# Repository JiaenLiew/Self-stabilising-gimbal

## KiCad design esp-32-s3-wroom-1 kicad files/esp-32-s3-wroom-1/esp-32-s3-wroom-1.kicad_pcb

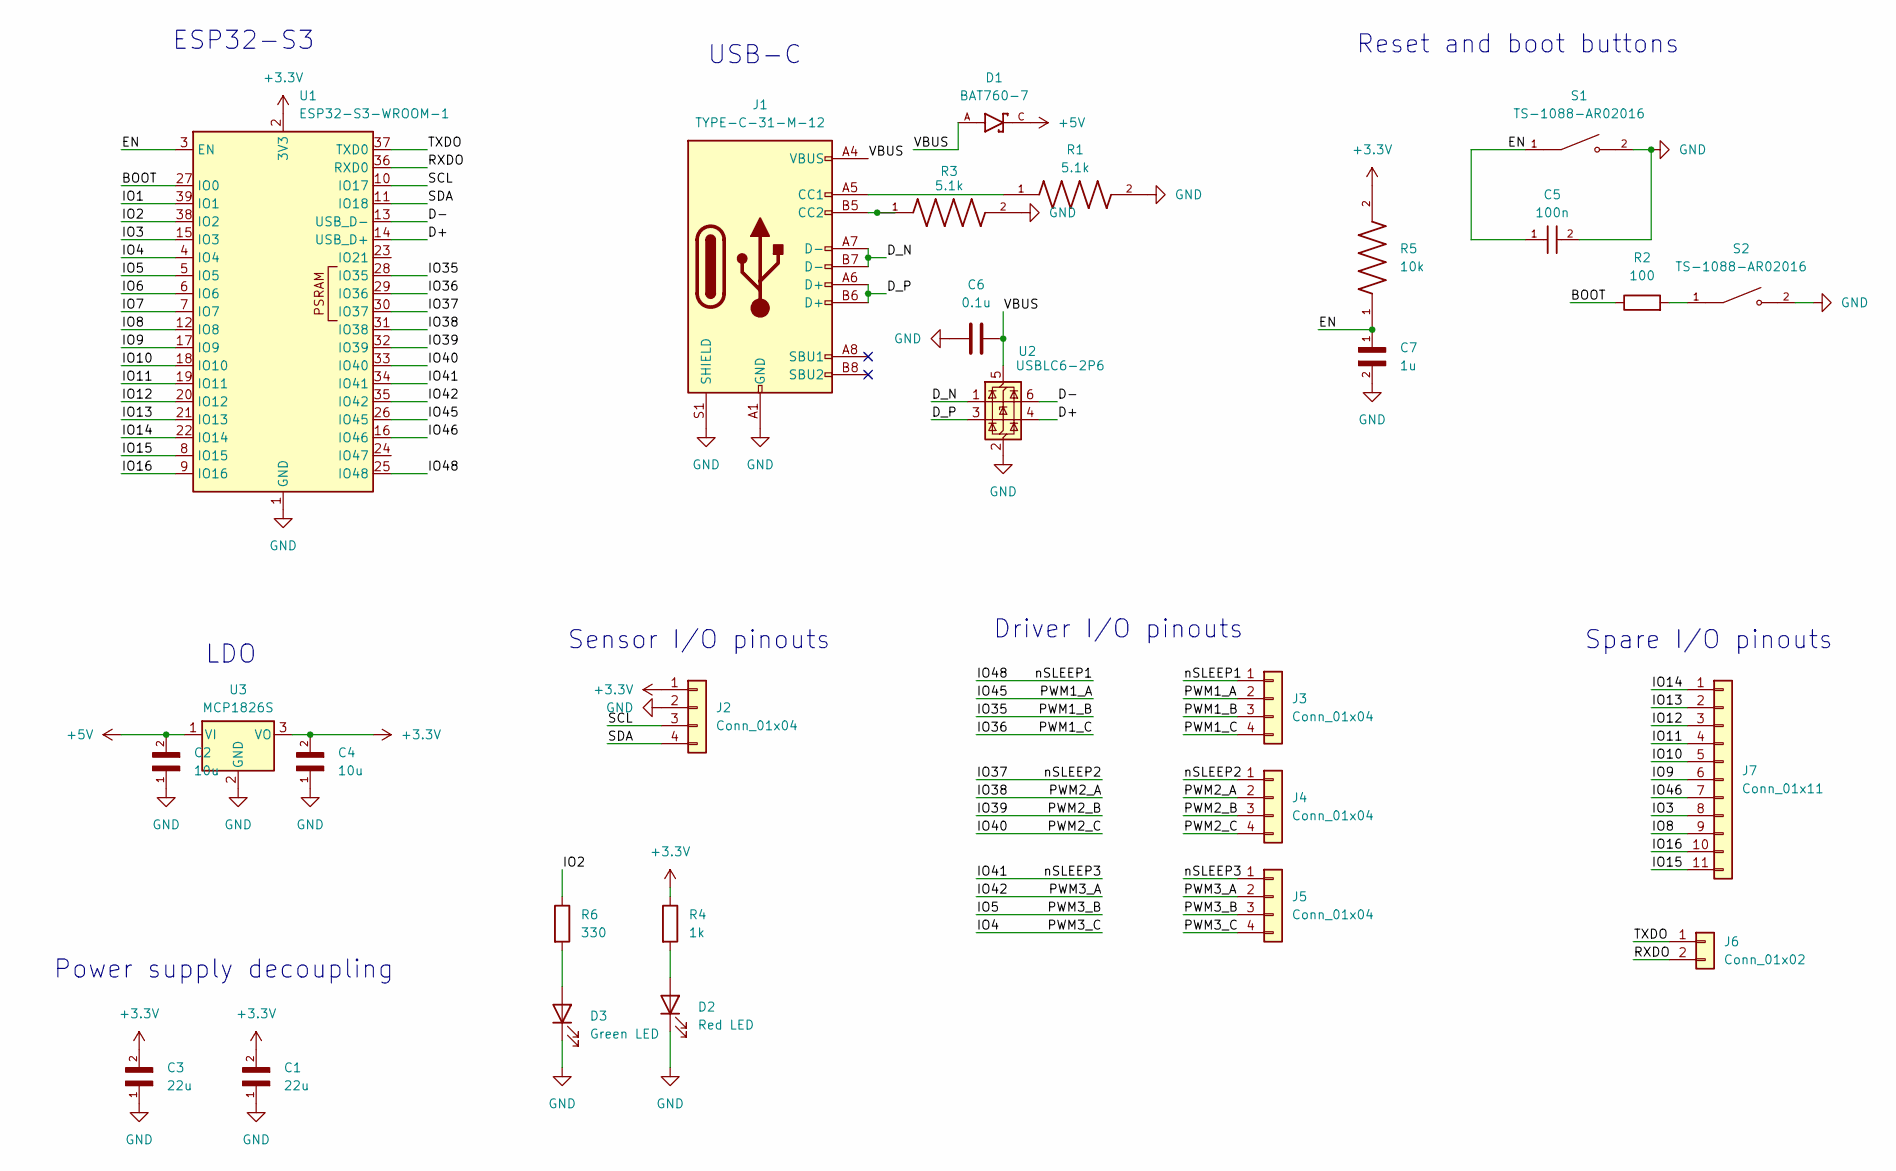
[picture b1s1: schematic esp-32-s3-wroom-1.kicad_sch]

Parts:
C1, C3: 22u; C_0805_2012Metric_Pad1.18x1.45mm_HandSolder
C2, C4: 10u; C_0805_2012Metric_Pad1.18x1.45mm_HandSolder
C5: 100n; C_0805_2012Metric_Pad1.18x1.45mm_HandSolder; DigiKey_Part_Number 732-7478-2-ND
C6: 0.1u; C_0805_2012Metric_Pad1.18x1.45mm_HandSolder
C7: 1u; C_0805_2012Metric_Pad1.18x1.45mm_HandSolder; DigiKey_Part_Number 490-5810-2-ND
D1: BAT760-7; SOD2513X120N; PARTREV 9-2
D2: Red LED; LED_0805_2012Metric_Pad1.15x1.40mm_HandSolder
D3: Green LED; LED_0805_2012Metric_Pad1.15x1.40mm_HandSolder
J1: TYPE-C-31-M-12; USB_C_Receptacle_HRO_TYPE-C-31-M-12
J2, J3, J4, J5: Conn_01x04; PinHeader_1x04_P2.54mm_Vertical
J6: Conn_01x02; PinHeader_1x02_P2.54mm_Vertical
J7: Conn_01x11; PinHeader_1x11_P2.54mm_Vertical
R1: 5.1k; R_0805_2012Metric_Pad1.20x1.40mm_HandSolder; PARTREV 3/1/2020; DigiKey_Part_Number P5.1KBRTR-ND
R2: 100; R_0805_2012Metric_Pad1.20x1.40mm_HandSolder
R3: 5.1k; C_0805_2012Metric_Pad1.18x1.45mm_HandSolder; PARTREV 3/1/2020; DigiKey_Part_Number P5.1KBRTR-ND
R4: 1k; R_0805_2012Metric_Pad1.20x1.40mm_HandSolder
R5: 10k; R_0805_2012Metric_Pad1.20x1.40mm_HandSolder; Voltage_Rating 50 V; Tolerance 5%; DigiKey_Part_Number A106045TR-ND
R6: 330; R_0805_2012Metric_Pad1.20x1.40mm_HandSolder
S1, S2: TS-1088-AR02016; SW_TS-1088-AR02016; PARTREV N/A
U1: ESP32-S3-WROOM-1
U2: USBLC6-2P6; SOT-666
U3: MCP1826S; SOT-223-3_TabPin2

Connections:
+3.3V: C1.2, C3.2, C4.2, J2.1, R4.1, R5.2, U1.2 (3V3), U3.3 (VO)
+5V: C2.2, D1.C, U3.1 (VI)
/BOOT: R2.1, U1.27 (IO0)
/D+: U1.14 (USB_D+), U2.4 (I/O2)
/D-: U1.13 (USB_D-), U2.6 (I/O1)
/D_N: J1.A7 (D-), J1.B7 (D-), U2.1 (I/O1)
/D_P: J1.A6 (D+), J1.B6 (D+), U2.3 (I/O2)
/EN: C5.1, C7.1, R5.1, S1.1, U1.3 (EN)
/IO1: U1.39 (IO1)
/IO2: R6.1, U1.38 (IO2)
/IO3: J7.8, U1.15 (IO3)
/IO4: J5.4, U1.4 (IO4)
/IO5: J5.3, U1.5 (IO5)
/IO6: U1.6 (IO6)
/IO7: U1.7 (IO7)
/IO8: J7.9, U1.12 (IO8)
/IO9: J7.6, U1.17 (IO9)
/IO10: J7.5, U1.18 (IO10)
/IO11: J7.4, U1.19 (IO11)
/IO12: J7.3, U1.20 (IO12)
/IO13: J7.2, U1.21 (IO13)
/IO14: J7.1, U1.22 (IO14)
/IO15: J7.11, U1.8 (IO15)
/IO16: J7.10, U1.9 (IO16)
/IO35: J3.3, U1.28 (IO35)
/IO36: J3.4, U1.29 (IO36)
/IO37: J4.1, U1.30 (IO37)
/IO38: J4.2, U1.31 (IO38)
/IO39: J4.3, U1.32 (IO39)
/IO40: J4.4, U1.33 (IO40)
/IO41: J5.1, U1.34 (IO41)
/IO42: J5.2, U1.35 (IO42)
/IO45: J3.2, U1.26 (IO45)
/IO46: J7.7, U1.16 (IO46)
/IO48: J3.1, U1.25 (IO48)
/RXDO: J6.2, U1.36 (RXD0)
/SCL: J2.3, U1.10 (IO17)
/SDA: J2.4, U1.11 (IO18)
/TXDO: J6.1, U1.37 (TXD0)
/VBUS: C6.2, D1.A, J1.A4 (VBUS), J1.A9 (VBUS), J1.B4 (VBUS), J1.B9 (VBUS), U2.5 (VBUS)
GND: C1.1, C2.1, C3.1, C4.1, C5.2, C6.1, C7.2, D2.1 (K), D3.1 (K), J1.A1 (GND), J1.A12 (GND), J1.B1 (GND), J1.B12 (GND), J1.S1 (SHIELD), J2.2, R1.2, R3.2, S1.2, S2.2, U1.1 (GND), U1.40 (GND), U1.41 (GND), U2.2 (GND), U3.2 (GND)
unnamed: D2.2 (A), R4.2
unnamed: D3.2 (A), R6.2
unnamed: J1.A5 (CC1), R1.1
unnamed: J1.B5 (CC2), R3.1
unnamed: R2.2, S2.1

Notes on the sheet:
USB-C
Sensor I/O pinouts
Reset and boot buttons
LDO
Power supply decoupling
Driver I/O pinouts
Spare I/O pinouts
ESP32-S3

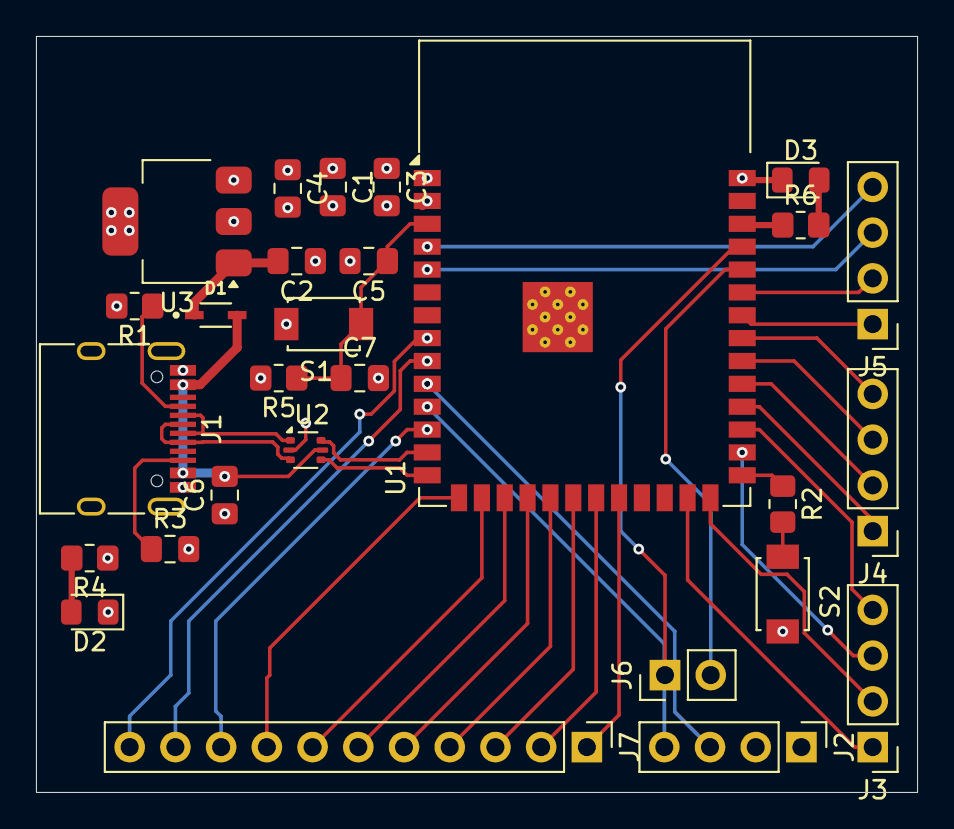
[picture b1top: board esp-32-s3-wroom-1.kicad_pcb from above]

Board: 4 copper layers, 49.0 x 42.0 mm, 28 parts (0 on the bottom side), 43 nets.

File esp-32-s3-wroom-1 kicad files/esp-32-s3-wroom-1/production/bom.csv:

Designator,Footprint,Quantity,Value,LCSC Part #
"C1, C3",0805,2,22u,
"C2, C4",0805,2,10u,
C5,0805,1,100n,
C6,0805,1,0.1u,
C7,0805,1,1u,
D1,SOD2513X120N,1,BAT760-7,
D2,0805,1,Red LED,
D3,0805,1,Green LED,
J1,USB_C_Receptacle_HRO_TYPE-C-31-M-12,1,TYPE-C-31-M-12,
"J2, J3, J4, J5",PinHeader_1x04_P2.54mm_Vertical,4,Conn_01x04,
J6,PinHeader_1x02_P2.54mm_Vertical,1,Conn_01x02,
J7,PinHeader_1x11_P2.54mm_Vertical,1,Conn_01x11,
"R1, R3",0805,2,5.1k,
R2,0805,1,100,
R4,0805,1,1k,
R5,0805,1,10k,
R6,0805,1,330,
"S1, S2",SW_TS-1088-AR02016,2,TS-1088-AR02016,
U1,ESP32-S3-WROOM-1,1,ESP32-S3-WROOM-1,
U2,SOT-666,1,USBLC6-2P6,
U3,SOT-223-3_TabPin2,1,MCP1826S,

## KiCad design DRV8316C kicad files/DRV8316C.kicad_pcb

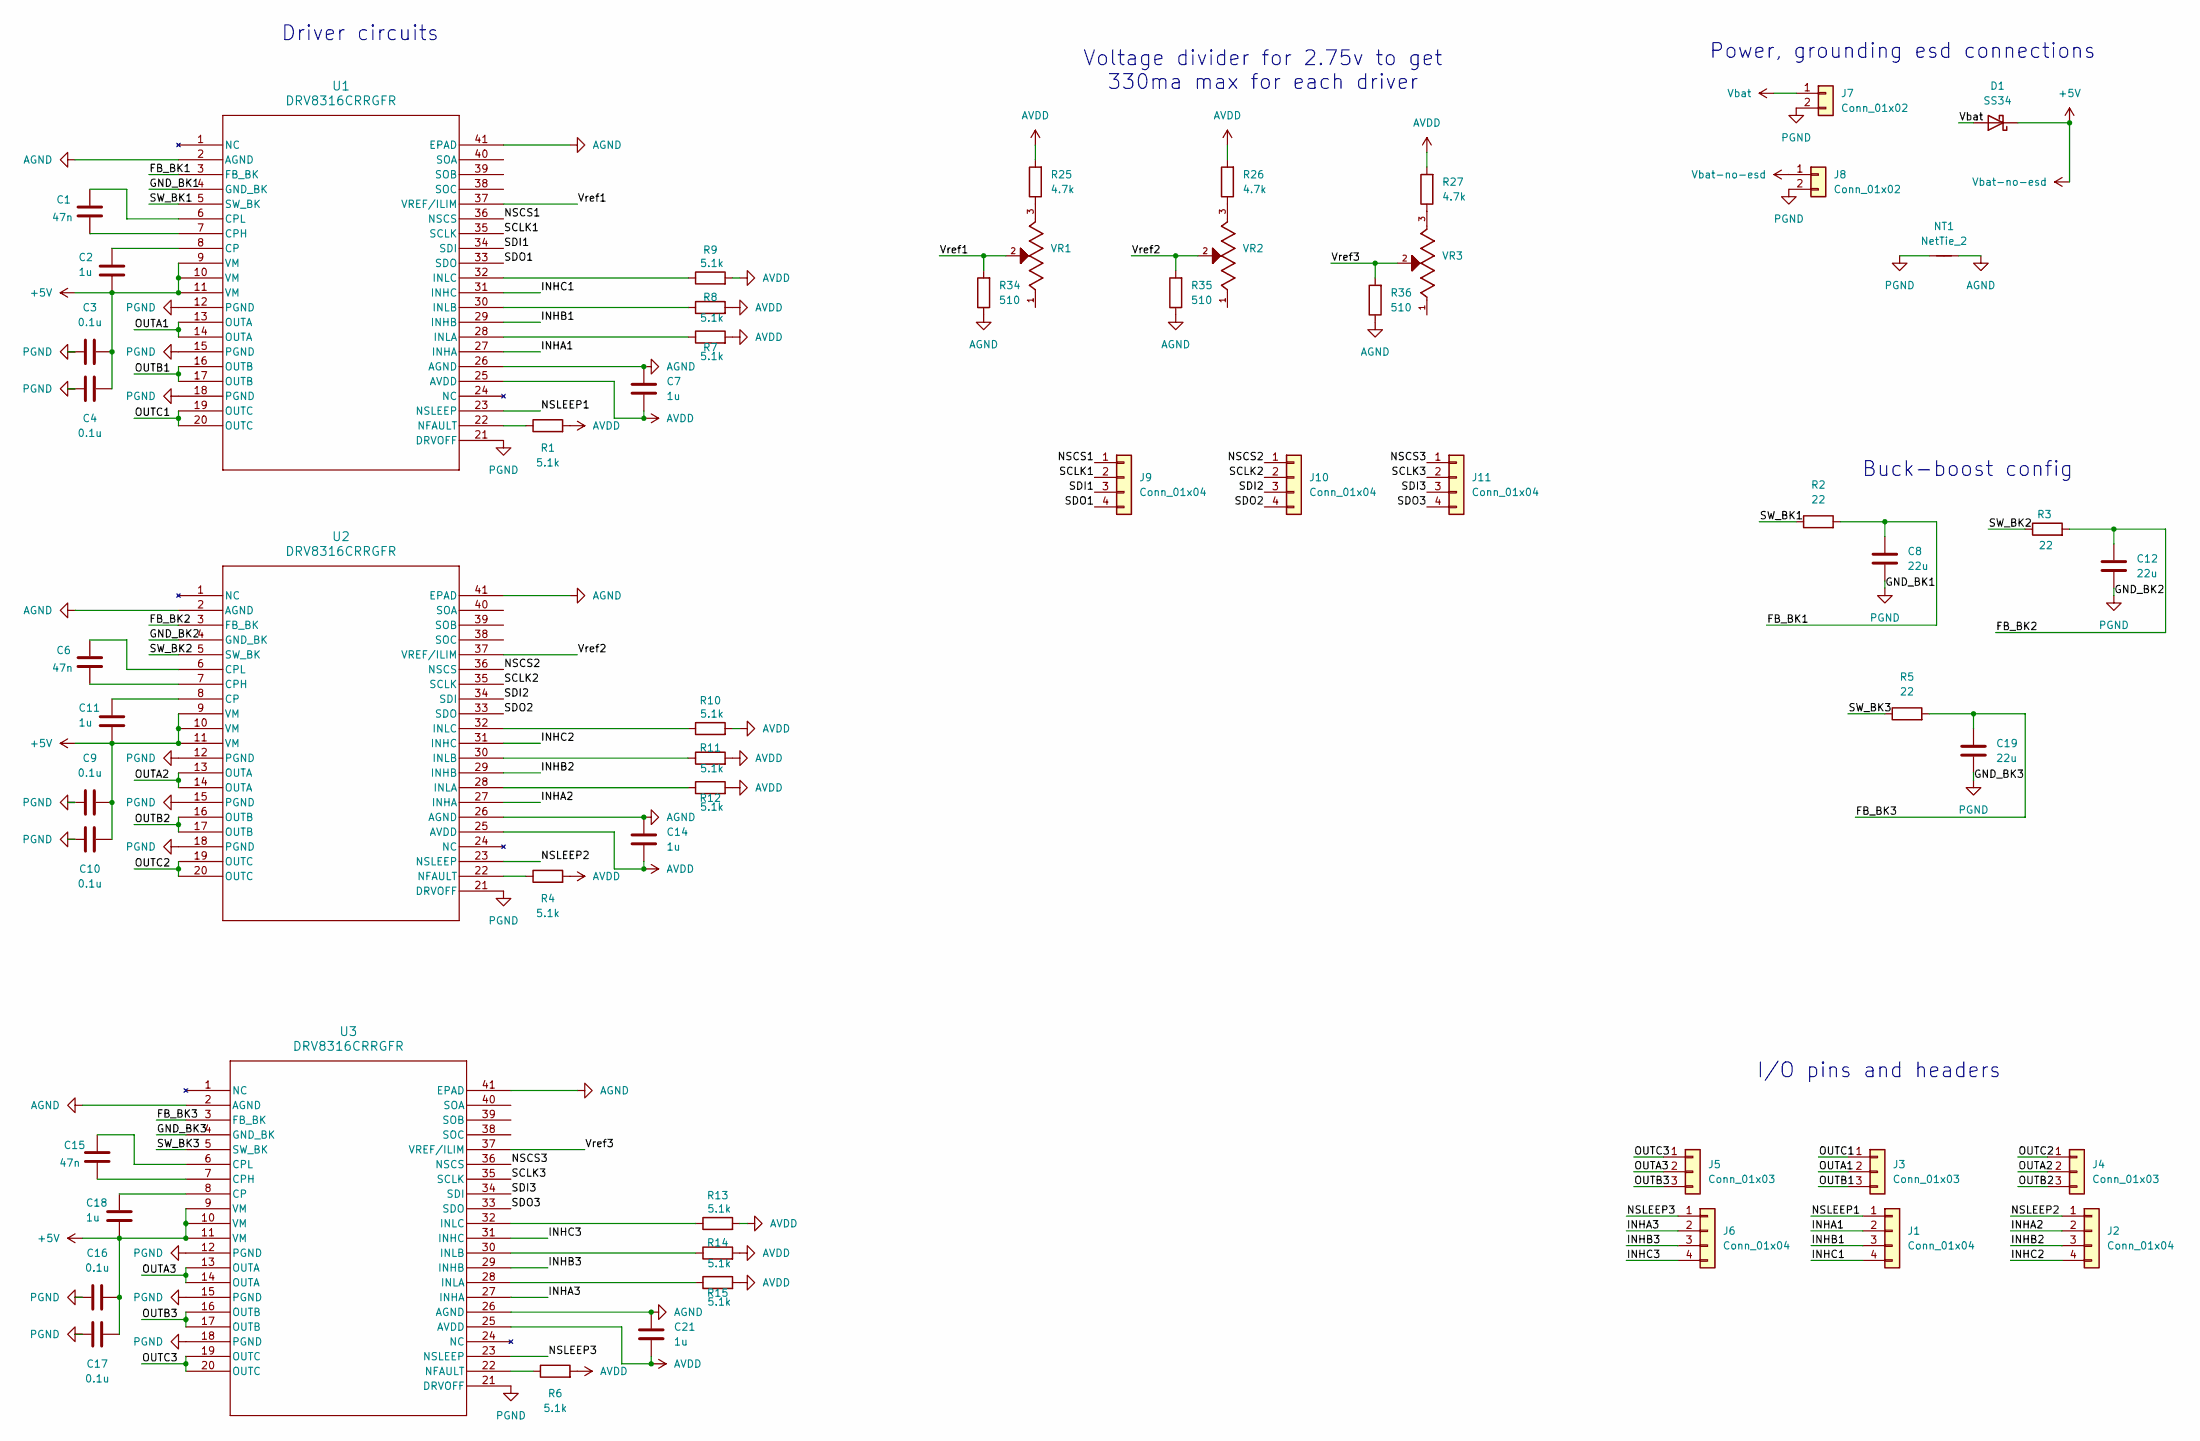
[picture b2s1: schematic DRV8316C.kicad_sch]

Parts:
C1, C6, C15: 47n; C_0805_2012Metric_Pad1.18x1.45mm_HandSolder
C2, C7, C11, C14, C18, C21: 1u; C_0805_2012Metric_Pad1.18x1.45mm_HandSolder
C3, C4, C9, C10, C16, C17: 0.1u; C_0805_2012Metric_Pad1.18x1.45mm_HandSolder
C8, C12, C19: 22u; C_0805_2012Metric_Pad1.18x1.45mm_HandSolder
D1: SS34; D_SMA
J1, J2, J6, J9, J10, J11: Conn_01x04; PinSocket_1x04_P2.54mm_Vertical
J3, J4, J5: Conn_01x03; PinHeader_1x03_P2.54mm_Vertical
J7, J8: Conn_01x02; PinSocket_1x02_P2.54mm_Vertical
NT1: NetTie_2
R1, R4, R6, R7, R8, R9, R10, R11, R12, R13, R14, R15: 5.1k; R_0805_2012Metric_Pad1.20x1.40mm_HandSolder
R2, R3, R5: 22; R_0805_2012Metric_Pad1.20x1.40mm_HandSolder
R25, R26, R27: 4.7k; R_0805_2012Metric_Pad1.20x1.40mm_HandSolder
R34, R35, R36: 510; R_0805_2012Metric_Pad1.20x1.40mm_HandSolder
U1, U2, U3: DRV8316CRRGFR; VQFN40_RGF_TEX
VR1, VR2, VR3: 3296W-1-103RLF; Potentiometer_Bourns_3296W_Vertical; PARTREV 05/16

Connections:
+5V: C2.2, C3.2, C4.2, C9.2, C10.2, C11.2, C16.2, C17.2, C18.2, D1.1 (K), J8.1, U1.9 (VM), U1.10 (VM), U1.11 (VM), U2.9 (VM), U2.10 (VM), U2.11 (VM), U3.9 (VM), U3.10 (VM), U3.11 (VM)
/FB_BK1: C8.1, R2.2, U1.3 (FB_BK)
/FB_BK2: C12.1, R3.2, U2.3 (FB_BK)
/FB_BK3: C19.1, R5.2, U3.3 (FB_BK)
/INHA1: J1.2, U1.27 (INHA)
/INHA2: J2.2, U2.27 (INHA)
/INHA3: J6.2, U3.27 (INHA)
/INHB1: J1.3, U1.29 (INHB)
/INHB2: J2.3, U2.29 (INHB)
/INHB3: J6.3, U3.29 (INHB)
/INHC1: J1.4, U1.31 (INHC)
/INHC2: J2.4, U2.31 (INHC)
/INHC3: J6.4, U3.31 (INHC)
/NSCS1: J9.1, U1.36 (NSCS)
/NSCS2: J10.1, U2.36 (NSCS)
/NSCS3: J11.1, U3.36 (NSCS)
/NSLEEP1: J1.1, U1.23 (NSLEEP)
/NSLEEP2: J2.1, U2.23 (NSLEEP)
/NSLEEP3: J6.1, U3.23 (NSLEEP)
/OUTA1: J3.2, U1.13 (OUTA), U1.14 (OUTA)
/OUTA2: J4.2, U2.13 (OUTA), U2.14 (OUTA)
/OUTA3: J5.2, U3.13 (OUTA), U3.14 (OUTA)
/OUTB1: J3.3, U1.16 (OUTB), U1.17 (OUTB)
/OUTB2: J4.3, U2.16 (OUTB), U2.17 (OUTB)
/OUTB3: J5.3, U3.16 (OUTB), U3.17 (OUTB)
/OUTC1: J3.1, U1.19 (OUTC), U1.20 (OUTC)
/OUTC2: J4.1, U2.19 (OUTC), U2.20 (OUTC)
/OUTC3: J5.1, U3.19 (OUTC), U3.20 (OUTC)
/SCLK1: J9.2, U1.35 (SCLK)
/SCLK2: J10.2, U2.35 (SCLK)
/SCLK3: J11.2, U3.35 (SCLK)
/SDI1: J9.3, U1.34 (SDI)
/SDI2: J10.3, U2.34 (SDI)
/SDI3: J11.3, U3.34 (SDI)
/SDO1: J9.4, U1.33 (SDO)
/SDO2: J10.4, U2.33 (SDO)
/SDO3: J11.4, U3.33 (SDO)
/SW_BK1: R2.1, U1.5 (SW_BK)
/SW_BK2: R3.1, U2.5 (SW_BK)
/SW_BK3: R5.1, U3.5 (SW_BK)
/Vref1: R34.2, U1.37 (VREF/ILIM), VR1.2
/Vref2: R35.2, U2.37 (VREF/ILIM), VR2.2
/Vref3: R36.2, U3.37 (VREF/ILIM), VR3.2
AGND: C7.1, C14.1, C21.1, NT1.2, R34.1, R35.1, R36.1, U1.2 (AGND), U1.26 (AGND), U1.41 (EPAD), U2.2 (AGND), U2.26 (AGND), U2.41 (EPAD), U3.2 (AGND), U3.26 (AGND), U3.41 (EPAD)
AVDD: C7.2, C14.2, C21.2, R1.2, R4.2, R6.2, R7.2, R8.2, R9.2, R10.2, R11.2, R12.2, R13.2, R14.2, R15.2, R25.2, R26.2, R27.2, U1.25 (AVDD), U2.25 (AVDD), U3.25 (AVDD)
unnamed: R25.1, VR1.3
unnamed: R26.1, VR2.3
unnamed: R27.1, VR3.3
unnamed: C2.1, U1.8 (CP)
unnamed: C1.2, U1.7 (CPH)
unnamed: C1.1, U1.6 (CPL)
unnamed: R7.1, U1.28 (INLA)
unnamed: R8.1, U1.30 (INLB)
unnamed: R9.1, U1.32 (INLC)
unnamed: R1.1, U1.22 (NFAULT)
unnamed: C11.1, U2.8 (CP)
unnamed: C6.2, U2.7 (CPH)
unnamed: C6.1, U2.6 (CPL)
unnamed: R12.1, U2.28 (INLA)
unnamed: R11.1, U2.30 (INLB)
unnamed: R10.1, U2.32 (INLC)
unnamed: R4.1, U2.22 (NFAULT)
unnamed: C18.1, U3.8 (CP)
unnamed: C15.2, U3.7 (CPH)
unnamed: C15.1, U3.6 (CPL)
unnamed: R15.1, U3.28 (INLA)
unnamed: R14.1, U3.30 (INLB)
unnamed: R13.1, U3.32 (INLC)
unnamed: R6.1, U3.22 (NFAULT)
PGND: C3.1, C4.1, C8.2, C9.1, C10.1, C12.2, C16.1, C17.1, C19.2, J7.2, J8.2, NT1.1, U1.4 (GND_BK), U1.12 (PGND), U1.15 (PGND), U1.18 (PGND), U1.21 (DRVOFF), U2.4 (GND_BK), U2.12 (PGND), U2.15 (PGND), U2.18 (PGND), U2.21 (DRVOFF), U3.4 (GND_BK), U3.12 (PGND), U3.15 (PGND), U3.18 (PGND), U3.21 (DRVOFF)
Vbat: D1.2 (A), J7.1

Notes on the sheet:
Voltage divider for 2.75v to get 330ma max for each driver
Driver circuits
Power, grounding esd connections
Buck-boost config
I/O pins and headers

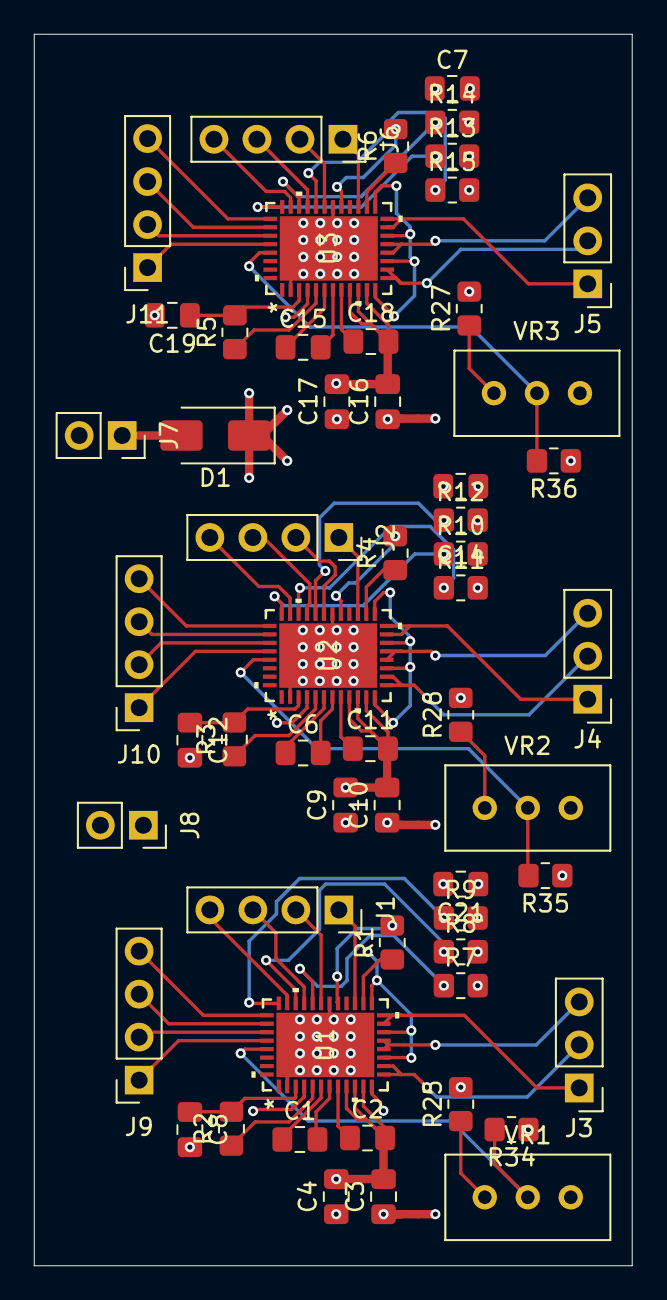
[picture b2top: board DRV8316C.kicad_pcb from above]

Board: 4 copper layers, 35.3 x 72.7 mm, 57 parts (0 on the bottom side), 71 nets.

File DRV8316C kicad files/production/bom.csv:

Designator,Footprint,Quantity,Value,LCSC Part #
"C1, C15, C6",0805,3,47n,
"C10, C16, C17, C3, C4, C9",0805,6,0.1u,
"C11, C14, C18, C2, C21, C7",0805,6,1u,
"C12, C19, C8",0805,3,22u,
D1,D_SMA,1,SS34,
"J1, J10, J11, J2, J6, J9",PinSocket_1x04_P2.54mm_Vertical,6,Conn_01x04,
"J3, J4, J5",PinHeader_1x03_P2.54mm_Vertical,3,Conn_01x03,
"J7, J8",PinSocket_1x02_P2.54mm_Vertical,2,Conn_01x02,
"R1, R10, R11, R12, R13, R14, R15, R4, R6, R7, R8, R9",0805,12,5.1k,
"R2, R3, R5",0805,3,22,
"R25, R26, R27",0805,3,4.7k,
"R34, R35, R36",0805,3,510,
"U1, U2, U3",VQFN40_RGF_TEX,3,DRV8316CRRGFR,
"VR1, VR2, VR3",Potentiometer_Bourns_3296W_Vertical,3,3296W-1-103RLF,

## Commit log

2025-07-26 This is our driver pcb designs with a potentiometer to regulate the max current for each individual driver, a power supply header with one having esd protection and the other having no esd protection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
2025-07-26 This is the ESP32-S3-WROOM-1 devboard which we chose as it provides high computing power to be able to perform 3 simultaneous PID control logics for each of the 3 axes of the gimbal. It also allows f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
